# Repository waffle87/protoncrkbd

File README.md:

### proton-c compatible crkbd pcb

### info
#### changes:
* usart full duplex communication (t**rr**s cable required!)
* move led data to pin with general purpose timer (ADC3-12/B0)
* add piezo buzzer (AST1109MLTRQ)
* add two rotary encoder positions
* add pimoroni trackball support (footprint thanks to [MangoIV](https://github.com/MangoIV))

firmware can be found at: [v1 (pre-2022)](https://github.com/waffle87/qmk.me/tree/e55177fb5b88a09c8d9882a33c33c5bfbc19e1fb/keymaps/crkbd) [v2 (current)](https://github.com/waffle87/qmk.me/tree/master/keymaps/crkbd)
(latest-commit pcbs are currently untested)

#### parts 
item | count
------------ | -------------
[1N4148 diodes (SOD-123)](https://www.aliexpress.com/item/3256802197190733) | 42
[SK6812 mini-e leds](https://www.aliexpress.com/item/4000475685852.html) | 42
[WS2812B leds](https://www.aliexpress.com/item/32732686773.html) | 12
[kailh mx sockets](https://www.aliexpress.com/item/4000019410050.html) | 42
[proton-c](https://qmk.fm/proton-c/) or [bonsai-c](https://github.com/customMK/Bonsai-C) | 2
[EC11 rotary encoders](https://www.aliexpress.com/item/2251832789732148) | 2
[PJ320A trrs jack](https://www.aliexpress.com/item/4000661212458.html) | 2
[reset switch](https://www.aliexpress.com/item/1255399892.html) | 2
[AST1109MLTRQ speakers](https://www.aliexpress.com/item/32558833519.html) | 2
[128x32 oled display](https://www.aliexpress.com/item/32794209149.html) | 2
[mcu/oled sockets](https://www.aliexpress.com/item/32847384633.html) | 2 (40 pos. each, 56 needed)
[oled socket pins](https://www.aliexpress.com/item/32855402975.html) | 1 (40 pos. each, 8 needed)
[mcu millmax pins](https://www.digikey.com/en/products/detail/mill-max-manufacturing-corp/3320-0-00-15-00-00-03-0/4147392) </br> alternatively, diode/resistor legs can be used | 48
pimoroni trackball [UK](https://shop.pimoroni.com/products/trackball-breakout) [EU](https://splitkb.com/collections/keyboard-parts/products/trackball-breakout) [NA](https://www.digikey.com/en/products/detail/pimoroni-ltd/PIM447/10246389) | 1

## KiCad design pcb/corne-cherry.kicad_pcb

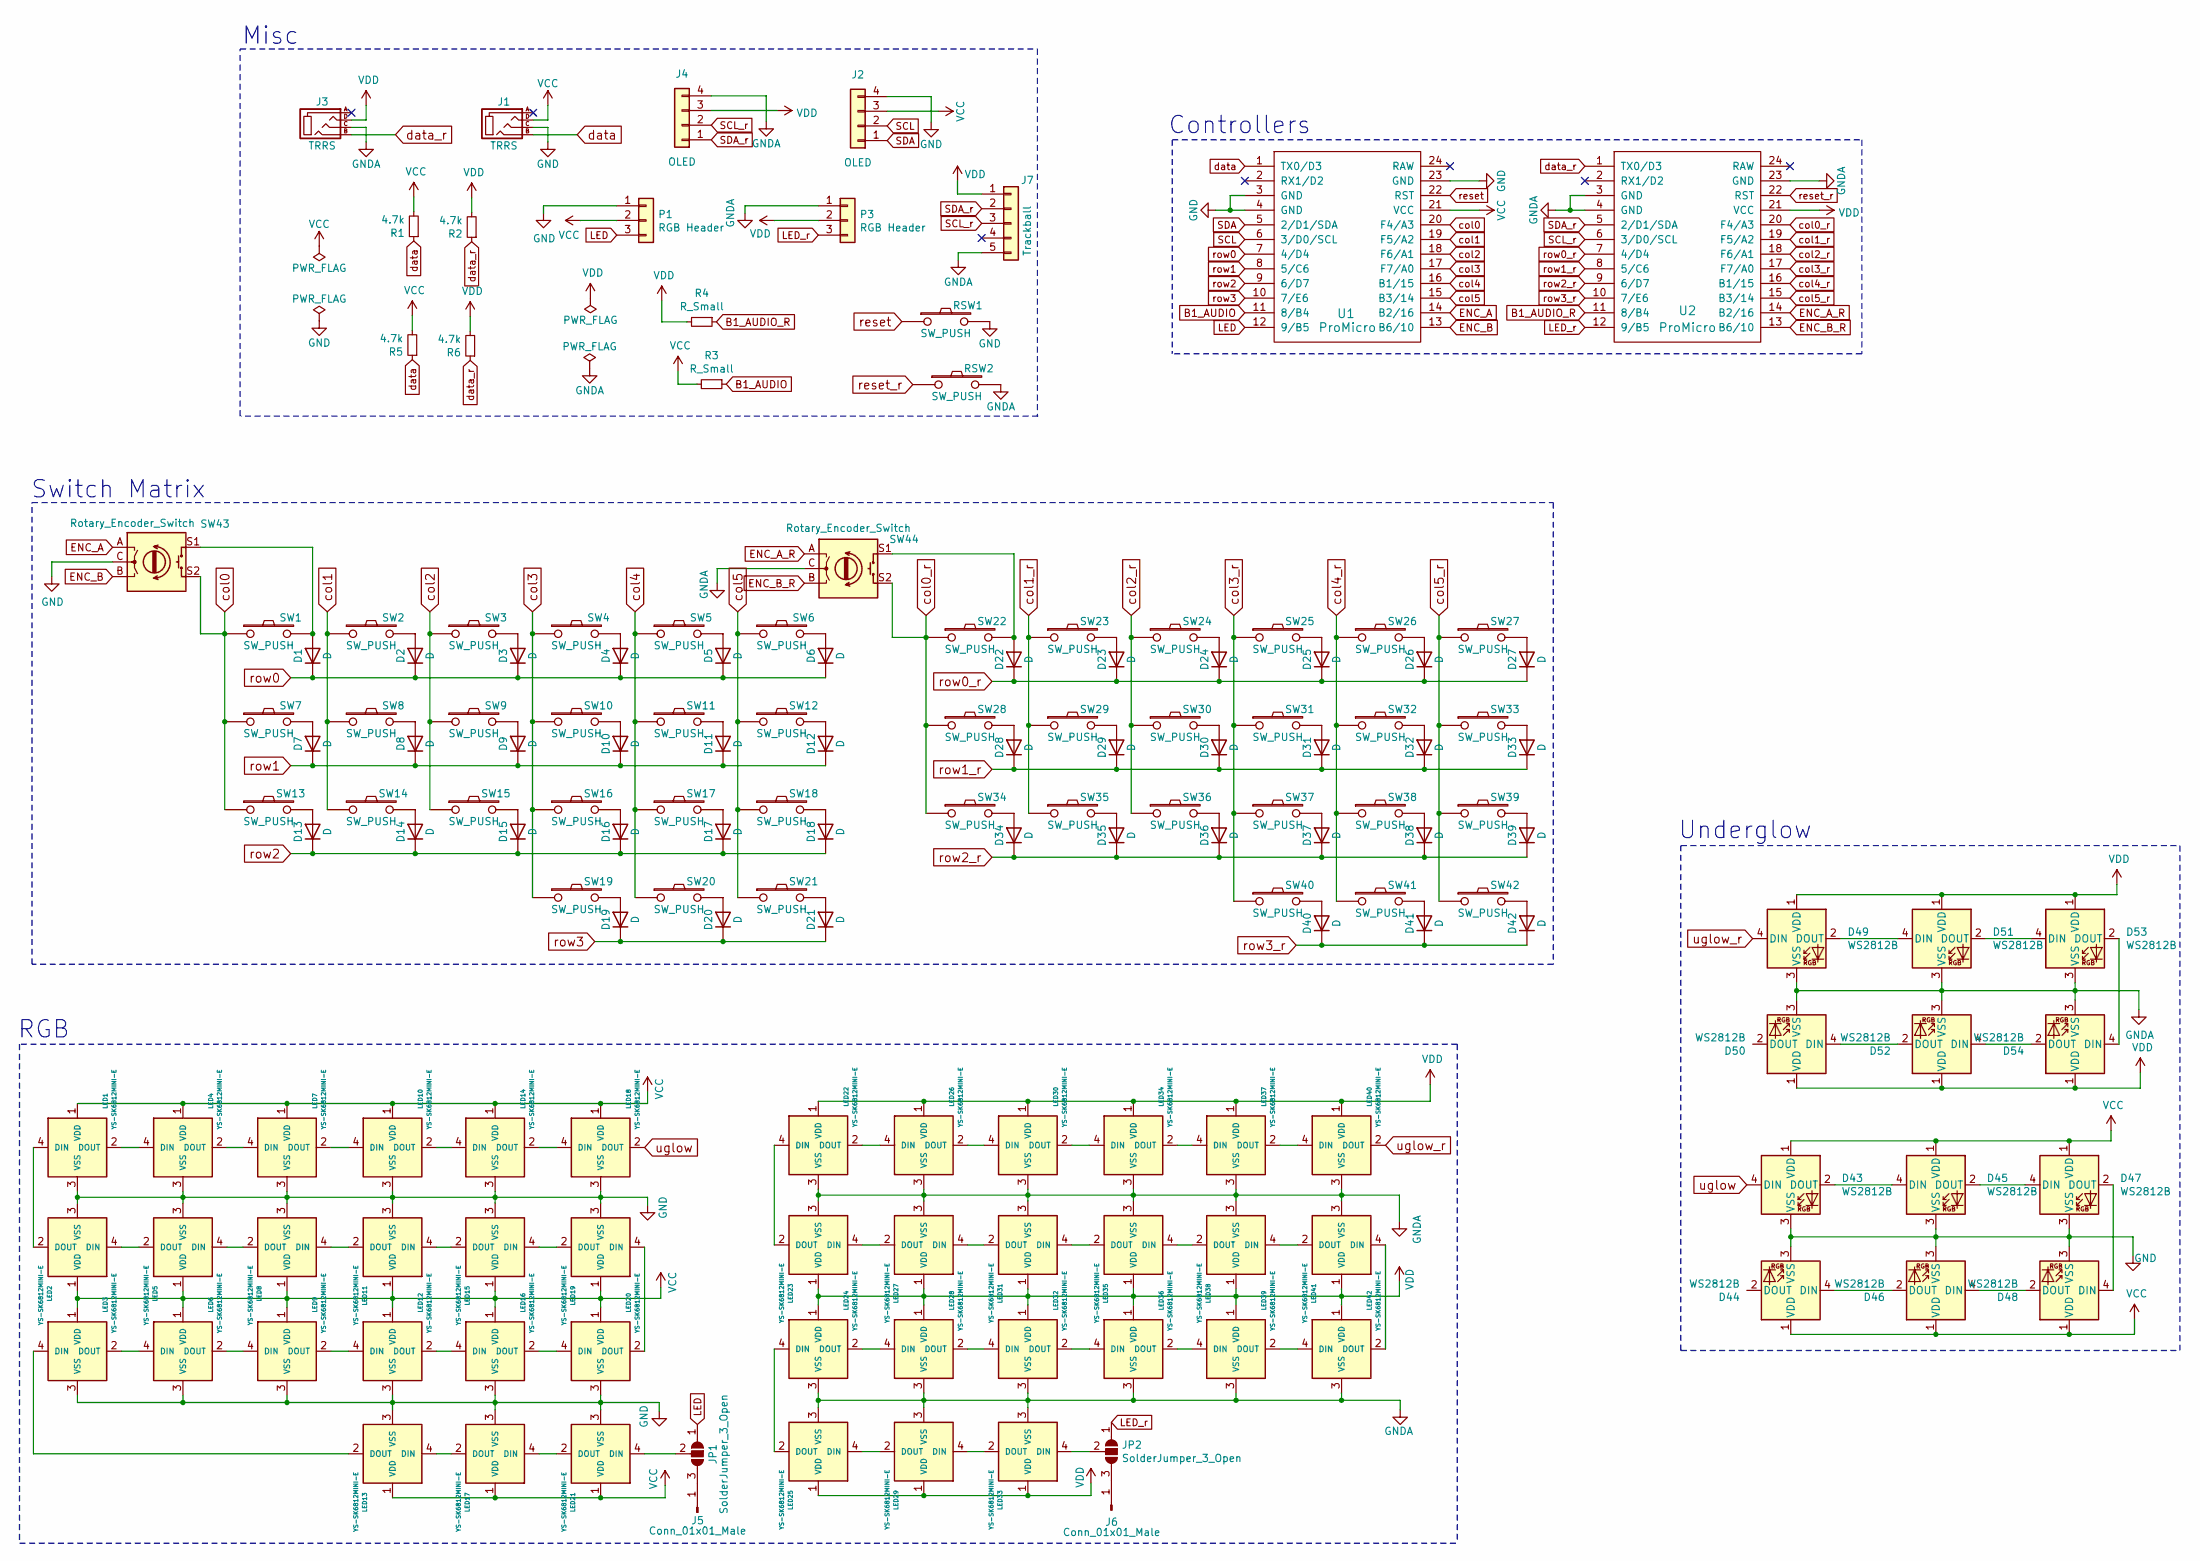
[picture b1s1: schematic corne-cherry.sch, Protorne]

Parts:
D1, D2, D3, D4, D5, D6, D7, D8, D9, D10, D11, D12, D13, D14, D15, D16, D17, D18, D19, D20, D21, D22, D23, D24, D25, D26, D27, D28, D29, D30, D31, D32, D33, D34, D35, D36, D37, D38, D39, D40, D41, D42: D; D3_SMD_v2; LCSC C402213
D43, D44, D45, D46, D47, D48, D49, D50, D51, D52, D53, D54: WS2812B
J1, J3: TRRS; MJ-4PP-9_1side
J2, J4: OLED; OLED_1side
J5, J6: Conn_01x01_Male; PinHeader_1x01_P2.54mm_Vertical
J7: Trackball; pimoroni_left_side_mount
JP1, JP2: SolderJumper_3_Open; SolderJumper-3_P1.3mm_Open_Pad1.0x1.5mm
LED1, LED2, LED3, LED4, LED5, LED6, LED7, LED8, LED9, LED10, LED11, LED12, LED13, LED14, LED15, LED16, LED17, LED18, LED19, LED20, LED21, LED22, LED23, LED24, LED25, LED26, LED27, LED28, LED29, LED30, LED31, LED32, LED33, LED34, LED35, LED36, LED37, LED38, LED39, LED40, LED41, LED42: YS-SK6812MINI-E
P1: RGB Header; PinSocket_1x03_P2.54mm_Vertical
P3: RGB Header; PinSocket_1x03_P2.54mm_Horizontal
R1, R2: 4.7k; R_Axial_DIN0207_L6.3mm_D2.5mm_P7.62mm_Horizontal
R3, R4: R_Small; Buzzer_Mallory_AST1109MLTRQ
R5, R6: 4.7k; R_0805
RSW1, RSW2: SW_PUSH; ResetSW_1side
SW1, SW2, SW3, SW4, SW5, SW6, SW7, SW8, SW9, SW10, SW11, SW12, SW13, SW14, SW15, SW16, SW17, SW18, SW19, SW20, SW22, SW23, SW24, SW25, SW26, SW27, SW28, SW29, SW30, SW31, SW32, SW33, SW34, SW35, SW36, SW37, SW38, SW39, SW40, SW41: SW_PUSH; CherryMX_Hotswap
SW21, SW42: SW_PUSH; CherryMX_Hotswap_1.5u
SW43, SW44: Rotary_Encoder_Switch; RotaryEncoder_EC11-no-legs
U1, U2: ProMicro; ProMicro_v3

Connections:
B1_AUDIO: R3.1, U1.11 (8/B4)
B1_AUDIO_R: R4.1, U2.11 (8/B4)
ENC_A: SW43.A, U1.14 (B2/16)
ENC_A_R: SW44.A, U2.14 (B2/16)
ENC_B: SW43.B, U1.13 (B6/10)
ENC_B_R: SW44.B, U2.13 (B6/10)
GND: D43.3 (VSS), D44.3 (VSS), D45.3 (VSS), D46.3 (VSS), D47.3 (VSS), D48.3 (VSS), J1.C, J2.4, LED1.3 (VSS), LED2.3 (VSS), LED3.3 (VSS), LED4.3 (VSS), LED5.3 (VSS), LED6.3 (VSS), LED7.3 (VSS), LED8.3 (VSS), LED9.3 (VSS), LED10.3 (VSS), LED11.3 (VSS), LED12.3 (VSS), LED13.3 (VSS), LED14.3 (VSS), LED15.3 (VSS), LED16.3 (VSS), LED17.3 (VSS), LED18.3 (VSS), LED19.3 (VSS), LED20.3 (VSS), LED21.3 (VSS), P1.1, RSW1.2, SW43.C, U1.3 (GND), U1.4 (GND), U1.23 (GND)
GNDA: D49.3 (VSS), D50.3 (VSS), D51.3 (VSS), D52.3 (VSS), D53.3 (VSS), D54.3 (VSS), J3.C, J4.4, J7.5, LED22.3 (VSS), LED23.3 (VSS), LED24.3 (VSS), LED25.3 (VSS), LED26.3 (VSS), LED27.3 (VSS), LED28.3 (VSS), LED29.3 (VSS), LED30.3 (VSS), LED31.3 (VSS), LED32.3 (VSS), LED33.3 (VSS), LED34.3 (VSS), LED35.3 (VSS), LED36.3 (VSS), LED37.3 (VSS), LED38.3 (VSS), LED39.3 (VSS), LED40.3 (VSS), LED41.3 (VSS), LED42.3 (VSS), P3.1, RSW2.2, SW44.C, U2.3 (GND), U2.4 (GND), U2.23 (GND)
LED: JP1.1 (A), P1.3, U1.12 (9/B5)
LED_r: JP2.1 (A), P3.3, U2.12 (9/B5)
unnamed: D1.2 (A), SW1.2, SW43.S1
unnamed: D2.2 (A), SW2.2
unnamed: D3.2 (A), SW3.2
unnamed: D4.2 (A), SW4.2
unnamed: D5.2 (A), SW5.2
unnamed: D6.2 (A), SW6.2
unnamed: D7.2 (A), SW7.2
unnamed: D8.2 (A), SW8.2
unnamed: D9.2 (A), SW9.2
unnamed: D10.2 (A), SW10.2
unnamed: D11.2 (A), SW11.2
unnamed: D12.2 (A), SW12.2
unnamed: D13.2 (A), SW13.2
unnamed: D14.2 (A), SW14.2
unnamed: D15.2 (A), SW15.2
unnamed: D16.2 (A), SW16.2
unnamed: D17.2 (A), SW17.2
unnamed: D18.2 (A), SW18.2
unnamed: D19.2 (A), SW19.2
unnamed: D20.2 (A), SW20.2
unnamed: D21.2 (A), SW21.2
unnamed: D22.2 (A), SW22.2, SW44.S1
unnamed: D23.2 (A), SW23.2
unnamed: D24.2 (A), SW24.2
unnamed: D25.2 (A), SW25.2
unnamed: D26.2 (A), SW26.2
unnamed: D27.2 (A), SW27.2
unnamed: D28.2 (A), SW28.2
unnamed: D29.2 (A), SW29.2
unnamed: D30.2 (A), SW30.2
unnamed: D31.2 (A), SW31.2
unnamed: D32.2 (A), SW32.2
unnamed: D33.2 (A), SW33.2
unnamed: D34.2 (A), SW34.2
unnamed: D35.2 (A), SW35.2
unnamed: D36.2 (A), SW36.2
unnamed: D37.2 (A), SW37.2
unnamed: D38.2 (A), SW38.2
unnamed: D39.2 (A), SW39.2
unnamed: D40.2 (A), SW40.2
unnamed: D41.2 (A), SW41.2
unnamed: D42.2 (A), SW42.2
unnamed: D43.2 (DOUT), D45.4 (DIN)
unnamed: D44.4 (DIN), D46.2 (DOUT)
unnamed: D45.2 (DOUT), D47.4 (DIN)
unnamed: D46.4 (DIN), D48.2 (DOUT)
unnamed: D47.2 (DOUT), D48.4 (DIN)
unnamed: D49.2 (DOUT), D51.4 (DIN)
unnamed: D50.4 (DIN), D52.2 (DOUT)
unnamed: D51.2 (DOUT), D53.4 (DIN)
unnamed: D52.4 (DIN), D54.2 (DOUT)
unnamed: D53.2 (DOUT), D54.4 (DIN)
unnamed: J5.1, JP1.3 (B)
unnamed: J6.1, JP2.3 (B)
unnamed: JP1.2 (C), LED21.4 (DIN)
unnamed: JP2.2 (C), LED33.4 (DIN)
unnamed: LED1.2 (DOUT), LED4.4 (DIN)
unnamed: LED1.4 (DIN), LED2.2 (DOUT)
unnamed: LED2.4 (DIN), LED5.2 (DOUT)
unnamed: LED3.2 (DOUT), LED6.4 (DIN)
unnamed: LED4.2 (DOUT), LED7.4 (DIN)
unnamed: LED5.4 (DIN), LED8.2 (DOUT)
unnamed: LED6.2 (DOUT), LED9.4 (DIN)
unnamed: LED10.2 (DOUT), LED14.4 (DIN)
unnamed: LED7.2 (DOUT), LED10.4 (DIN)
unnamed: LED8.4 (DIN), LED11.2 (DOUT)
unnamed: LED11.4 (DIN), LED15.2 (DOUT)
unnamed: LED12.2 (DOUT), LED16.4 (DIN)
unnamed: LED9.2 (DOUT), LED12.4 (DIN)
unnamed: LED3.4 (DIN), LED13.2 (DOUT)
unnamed: LED13.4 (DIN), LED17.2 (DOUT)
unnamed: LED14.2 (DOUT), LED18.4 (DIN)
unnamed: LED15.4 (DIN), LED19.2 (DOUT)
unnamed: LED16.2 (DOUT), LED20.4 (DIN)
unnamed: LED17.4 (DIN), LED21.2 (DOUT)
unnamed: LED19.4 (DIN), LED20.2 (DOUT)
unnamed: LED22.2 (DOUT), LED26.4 (DIN)
unnamed: LED22.4 (DIN), LED23.2 (DOUT)
unnamed: LED23.4 (DIN), LED27.2 (DOUT)
unnamed: LED24.2 (DOUT), LED28.4 (DIN)
unnamed: LED24.4 (DIN), LED25.2 (DOUT)
unnamed: LED25.4 (DIN), LED29.2 (DOUT)
unnamed: LED26.2 (DOUT), LED30.4 (DIN)
unnamed: LED27.4 (DIN), LED31.2 (DOUT)
unnamed: LED28.2 (DOUT), LED32.4 (DIN)
unnamed: LED29.4 (DIN), LED33.2 (DOUT)
unnamed: LED30.2 (DOUT), LED34.4 (DIN)
unnamed: LED31.4 (DIN), LED35.2 (DOUT)
unnamed: LED32.2 (DOUT), LED36.4 (DIN)
unnamed: LED34.2 (DOUT), LED37.4 (DIN)
unnamed: LED35.4 (DIN), LED38.2 (DOUT)
unnamed: LED36.2 (DOUT), LED39.4 (DIN)
unnamed: LED37.2 (DOUT), LED40.4 (DIN)
unnamed: LED38.4 (DIN), LED41.2 (DOUT)
unnamed: LED39.2 (DOUT), LED42.4 (DIN)
unnamed: LED41.4 (DIN), LED42.2 (DOUT)
SCL: J2.2, U1.6 (3/D0/SCL)
SCL_r: J4.2, J7.3, U2.6 (3/D0/SCL)
SDA: J2.1, U1.5 (2/D1/SDA)
SDA_r: J4.1, J7.2, U2.5 (2/D1/SDA)
VCC: D43.1 (VDD), D44.1 (VDD), D45.1 (VDD), D46.1 (VDD), D47.1 (VDD), D48.1 (VDD), J1.D, J2.3, LED1.1 (VDD), LED2.1 (VDD), LED3.1 (VDD), LED4.1 (VDD), LED5.1 (VDD), LED6.1 (VDD), LED7.1 (VDD), LED8.1 (VDD), LED9.1 (VDD), LED10.1 (VDD), LED11.1 (VDD), LED12.1 (VDD), LED13.1 (VDD), LED14.1 (VDD), LED15.1 (VDD), LED16.1 (VDD), LED17.1 (VDD), LED18.1 (VDD), LED19.1 (VDD), LED20.1 (VDD), LED21.1 (VDD), P1.2, R1.2, R3.2, R5.2, U1.21 (VCC)
VDD: D49.1 (VDD), D50.1 (VDD), D51.1 (VDD), D52.1 (VDD), D53.1 (VDD), D54.1 (VDD), J3.D, J4.3, J7.1, LED22.1 (VDD), LED23.1 (VDD), LED24.1 (VDD), LED25.1 (VDD), LED26.1 (VDD), LED27.1 (VDD), LED28.1 (VDD), LED29.1 (VDD), LED30.1 (VDD), LED31.1 (VDD), LED32.1 (VDD), LED33.1 (VDD), LED34.1 (VDD), LED35.1 (VDD), LED36.1 (VDD), LED37.1 (VDD), LED38.1 (VDD), LED39.1 (VDD), LED40.1 (VDD), LED41.1 (VDD), LED42.1 (VDD), P3.2, R2.2, R4.2, R6.2, U2.21 (VCC)
col0: SW1.1, SW7.1, SW13.1, SW43.S2, U1.20 (F4/A3)
col0_r: SW22.1, SW28.1, SW34.1, SW44.S2, U2.20 (F4/A3)
col1: SW2.1, SW8.1, SW14.1, U1.19 (F5/A2)
col1_r: SW23.1, SW29.1, SW35.1, U2.19 (F5/A2)
col2: SW3.1, SW9.1, SW15.1, U1.18 (F6/A1)
col2_r: SW24.1, SW30.1, SW36.1, U2.18 (F6/A1)
col3: SW4.1, SW10.1, SW16.1, SW19.1, U1.17 (F7/A0)
col3_r: SW25.1, SW31.1, SW37.1, SW40.1, U2.17 (F7/A0)
col4: SW5.1, SW11.1, SW17.1, SW20.1, U1.16 (B1/15)
col4_r: SW26.1, SW32.1, SW38.1, SW41.1, U2.16 (B1/15)
col5: SW6.1, SW12.1, SW18.1, SW21.1, U1.15 (B3/14)
col5_r: SW27.1, SW33.1, SW39.1, SW42.1, U2.15 (B3/14)
data: J1.B, R1.1, R5.1, U1.1 (TX0/D3)
data_r: J3.B, R2.1, R6.1, U2.1 (TX0/D3)
reset: RSW1.1, U1.22 (RST)
reset_r: RSW2.1, U2.22 (RST)
row0: D1.1 (K), D2.1 (K), D3.1 (K), D4.1 (K), D5.1 (K), D6.1 (K), U1.7 (4/D4)
row0_r: D22.1 (K), D23.1 (K), D24.1 (K), D25.1 (K), D26.1 (K), D27.1 (K), U2.7 (4/D4)
row1: D7.1 (K), D8.1 (K), D9.1 (K), D10.1 (K), D11.1 (K), D12.1 (K), U1.8 (5/C6)
row1_r: D28.1 (K), D29.1 (K), D30.1 (K), D31.1 (K), D32.1 (K), D33.1 (K), U2.8 (5/C6)
row2: D13.1 (K), D14.1 (K), D15.1 (K), D16.1 (K), D17.1 (K), D18.1 (K), U1.9 (6/D7)
row2_r: D34.1 (K), D35.1 (K), D36.1 (K), D37.1 (K), D38.1 (K), D39.1 (K), U2.9 (6/D7)
row3: D19.1 (K), D20.1 (K), D21.1 (K), U1.10 (7/E6)
row3_r: D40.1 (K), D41.1 (K), D42.1 (K), U2.10 (7/E6)
uglow: D43.4 (DIN), LED18.2 (DOUT)
uglow_r: D49.4 (DIN), LED40.2 (DOUT)

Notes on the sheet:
Controllers
RGB
Switch Matrix
Misc
Underglow

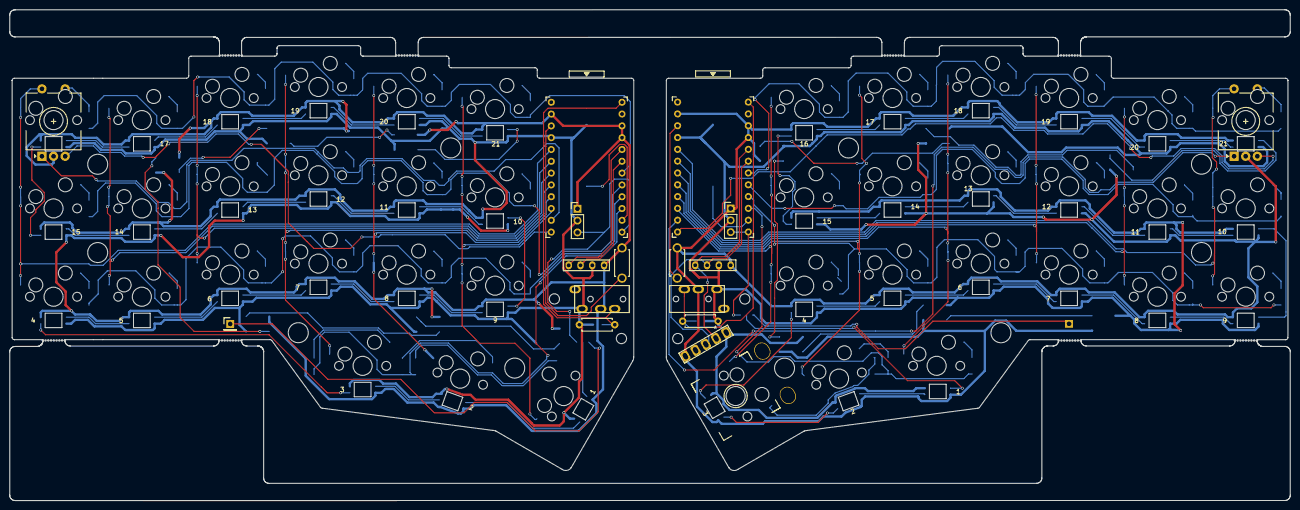
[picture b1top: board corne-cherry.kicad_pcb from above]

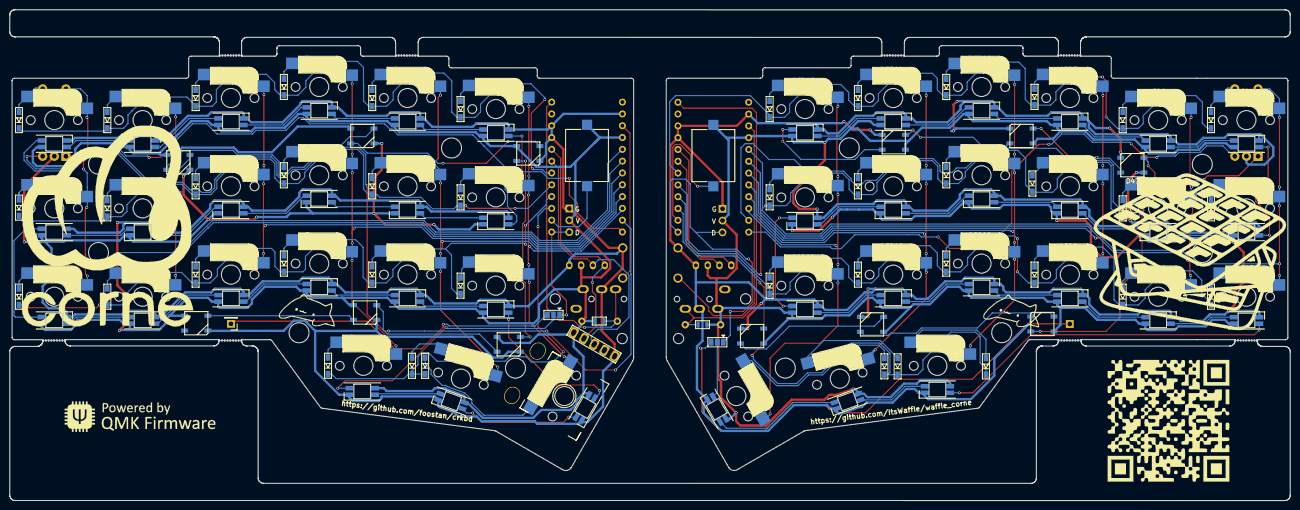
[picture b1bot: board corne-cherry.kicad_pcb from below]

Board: 2 copper layers, 275.5 x 105.6 mm, 175 parts (107 on the bottom side), 138 nets.

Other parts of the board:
Ref**: Val**; M2_HOLE_v2
Ref**#2, Ref**#3, Ref**#4, Ref**#5, Ref**#6, Ref**#7, Ref**#8, Ref**#9, Ref**#10, Ref**#11, Ref**#12, Ref**#13, Ref**#14: Val**; M2_HOLE_v2

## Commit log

2020-08-08 Upload Initial Files
2020-08-08 Add Some Unicode Stuff
2020-08-08 Update Unicode Info
2020-08-13 Updated Firmware
2020-08-13 Update glcdfont
2020-08-21 Genraal Update
2020-08-29 General Update
2020-09-15 Add Bongo Cat animation
2020-09-24 Add master OLED timeout
2020-09-24 Add image folder
2020-09-24 Image Update
2020-12-03 Giant overhaul
2020-12-03 Add mouse combos
2020-12-08 Add Fancy Unicode
2020-12-15 Add trackball support
2020-12-15 Update Macros
2020-12-18 Add Tap Dance Macros
2021-01-06 Add Nanoboot Bootloader Support
2021-01-09 Add GUI Layout
2021-01-10 General Updated
2021-01-11 More fixes
2021-01-11 Refactor and add PCB
2021-01-11 Add gerbers
2021-01-11 Begin readme
2021-01-15 Add working config!
2021-01-15 Update Gerbers
2021-01-17 Add PCB Image
2021-01-31 Add oled
2021-01-31 Add rand word generator
2021-02-09 Add inital RGB code & Sponebob typing mode
2021-02-09 Add header
2021-02-12 Add working RGB Config
2021-02-13 Add fully working config
2021-02-15 Cleanup
2021-02-19 Add Felix Typing Mode
2021-03-05 Firmware update - working
2021-03-24 Add kbd submodules
2021-03-24 Add RGB to left half
2021-03-24 Begin RGB placing and routing
2021-03-25 More rgb and fix G key
2021-03-25 Finish left half rgb
2021-03-25 Add speakers and RGB on right half
2021-03-26 Firmware Update
2021-03-26 Finish left half rgb with jumpers
2021-03-26 Place RGB
2021-03-26 Finish RGB on right half
2021-03-26 Update readme and add new PCB photos
2021-03-26 Update photos in readme
2021-03-26 Add silkscreen stuff
2021-03-27 Add v2 gerbers
2021-03-28 Finally add license lol
2021-03-29 Add PCB documentation
2021-03-29 Final gerbers
2021-04-07 Fix bad trace
2021-04-07 Update v2 gerbers
2021-04-08 Start reworking PCB
2021-04-08 Update more RGB stuff
2021-04-08 Almost done with RGB
2021-04-08 Finish RGB
2021-04-09 Add encoder to left half
2021-04-09 Finish PCB
2021-04-10 Add new images
2021-04-10 Clean up silks
2021-04-10 Clean up schematic
2021-04-23 change trace position - too close too mousebites
2021-04-23 Update readme and move info to wikim
2021-04-23 Update readme again
2021-04-24 Add default firmware stuff
2021-04-24 Update rgb num defines
2021-05-03 Silkscreen stuff on PCB and clean up schematiccm
2021-05-03 Add PDFs
2021-05-03 pdf in readme
2021-05-03 more readme stuff
2021-05-10 Update readme with new pdf stuff
2021-05-19 Clean up readme and other info stuff
2021-05-19 Add images
2021-05-19 Update readme with new images
2021-06-02 Update markers and silkscreen
2021-06-03 some underglow stuff on left half
2021-06-08 Finish underglow and add SMD resistor foorprints
2021-06-25 Fix RGB positions
2021-06-25 Update silkscreen
2021-06-28 Update images with new pcb
2021-07-26 Update firmware and clean up pcb
2022-11-21 misc
2022-11-21 clean up
2022-11-21 couple small changes
2022-11-25 add image & firmware links
2024-06-14 remove cache files
